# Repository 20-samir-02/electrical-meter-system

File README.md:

# electrical-meter-system
Power supply and embedded system design for smart electrical meter

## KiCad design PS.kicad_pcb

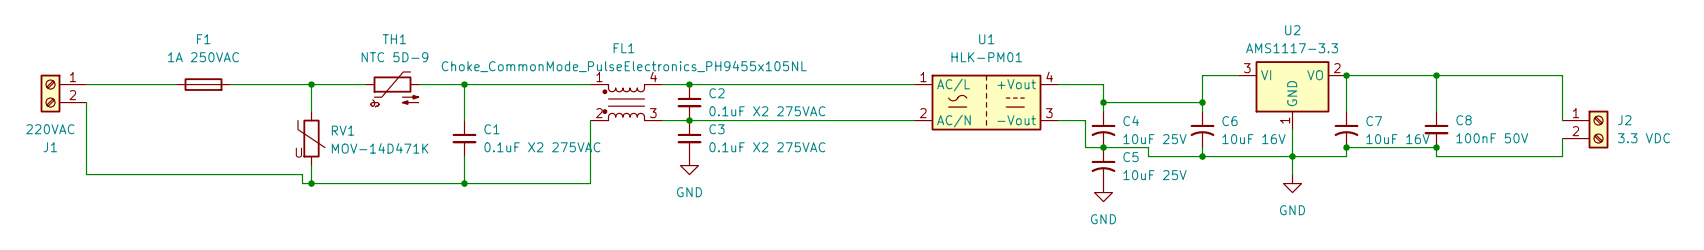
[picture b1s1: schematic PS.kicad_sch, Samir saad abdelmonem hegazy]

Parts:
C1, C2, C3: 0.1uF X2 275VAC; C_Radial_D16.0mm_H25.0mm_P7.50mm
C4, C5: 10uF 25V; CP_Radial_D5.0mm_P2.50mm
C6, C7: 10uF 16V; CP_Radial_D5.0mm_P2.50mm
C8: 100nF 50V; C_Disc_D5.0mm_W2.5mm_P5.00mm
F1: 1A 250VAC; Fuse_BelFuse_0ZRE0025FF_L9.6mm_W3.8mm
FL1: Choke_CommonMode_PulseElectronics_PH9455x105NL; L_CommonMode_PulseElectronics_PH9455x105NL_1
J1: 220VAC; TerminalBlock_MaiXu_MX126-5.0-02P_1x02_P5.00mm
J2: 3.3 VDC; TerminalBlock_MaiXu_MX126-5.0-02P_1x02_P5.00mm
RV1: MOV-14D471K; RV_Disc_D15.5mm_W3.9mm_P7.5mm
TH1: NTC 5D-9; RV_Disc_D9mm_W3.8mm_P5mm
U1: HLK-PM01; Converter_ACDC_Hi-Link_HLK-PMxx
U2: AMS1117-3.3; SOT-223-3_TabPin2

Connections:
GND: C3.2, C4.2, C5.1, C5.2, C6.2, C7.2, C8.2, J2.2, U1.3 (-Vout), U2.1 (GND)
unnamed: C1.1, FL1.1, TH1.2
unnamed: F1.2, RV1.1, TH1.1
unnamed: F1.1, J1.1
unnamed: C1.2, FL1.2, J1.2, RV1.2
unnamed: C7.1, C8.1, J2.1, U2.2 (VO)
unnamed: C4.1, C6.1, U1.4 (+Vout), U2.3 (VI)
unnamed: C2.1, FL1.4, U1.1 (AC/L)
unnamed: C2.2, C3.1, FL1.3, U1.2 (AC/N)

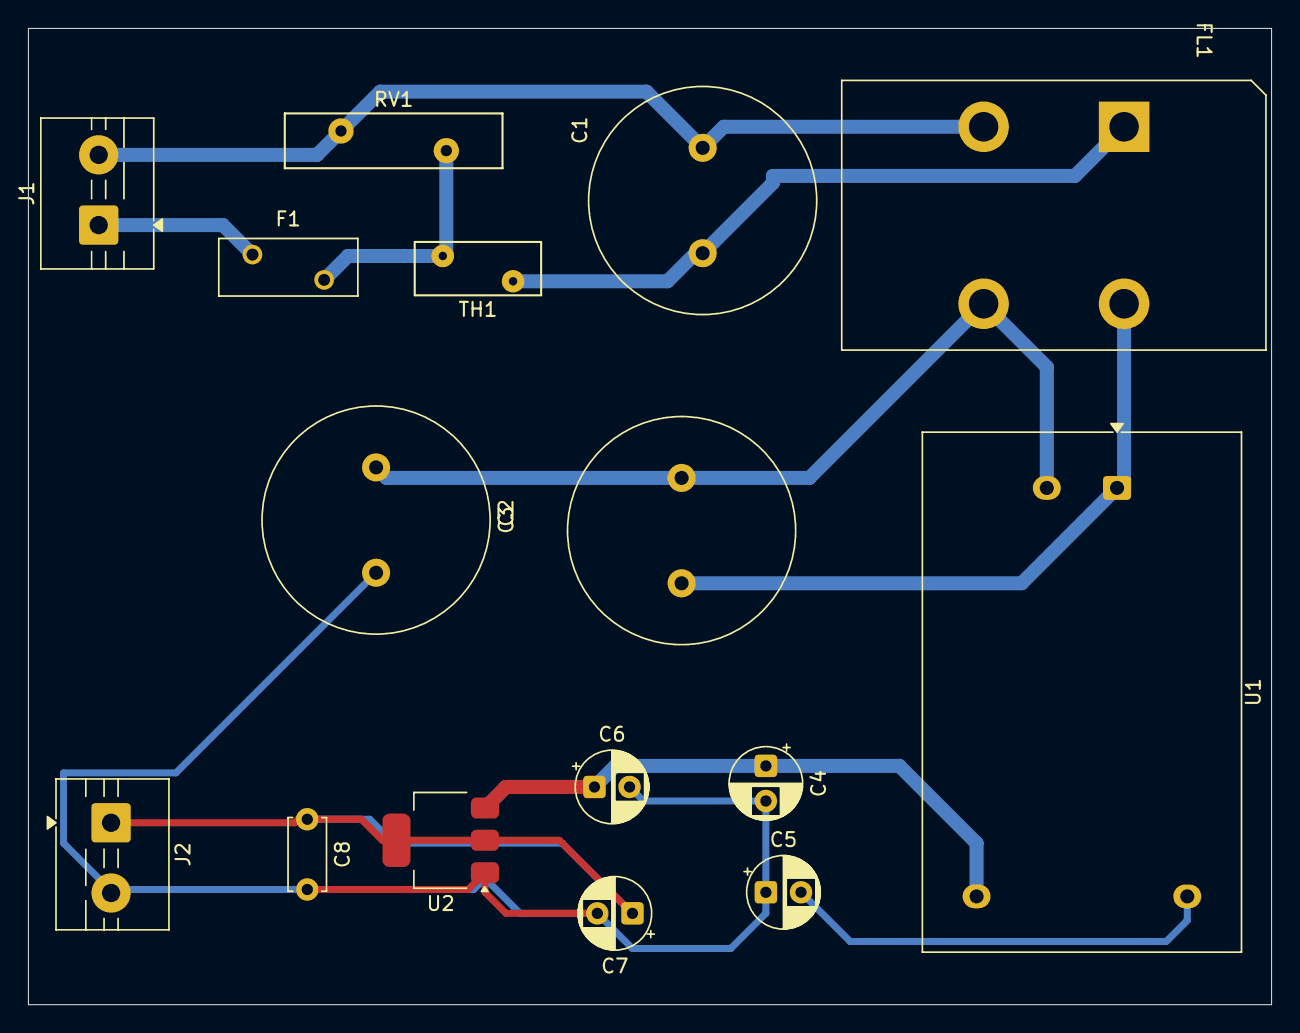
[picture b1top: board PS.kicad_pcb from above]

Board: 2 copper layers, 88.5 x 69.5 mm, 16 parts (0 on the bottom side), 9 nets.
